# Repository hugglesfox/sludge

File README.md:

# Sludge

Sludge is a hardware platform which is compatible with
[SlimeVR](https://slimevr.dev) firmware. Sludge is designed to be as
featureless and cost down as reasonable to provide a cheaper and updated
alternative to the official SlimeVR hardware.

## Features

- ESP32-C3 + Bosch BMI160
- Powered by a swappable AA battery
- Firmware flashing and hardware debugging over USB

## Does not feature

- Battery charging
- Expansion modules (e.g. for easier foot rotation tracking)

## TODO

- [X] General electrical design
- [ ] Clean up silk screen
- [ ] Switch to USB-C
- [ ] Physical design (straps, casing, etc.)
- [ ] Real world testing

## Licensing

Sludge (c) by Hayley Hughes and Contributors

Sludge is licensed under a
Creative Commons Attribution-ShareAlike 4.0 International License.

You should have received a copy of the license along with this
work. If not, see <http://creativecommons.org/licenses/by-sa/4.0/>.

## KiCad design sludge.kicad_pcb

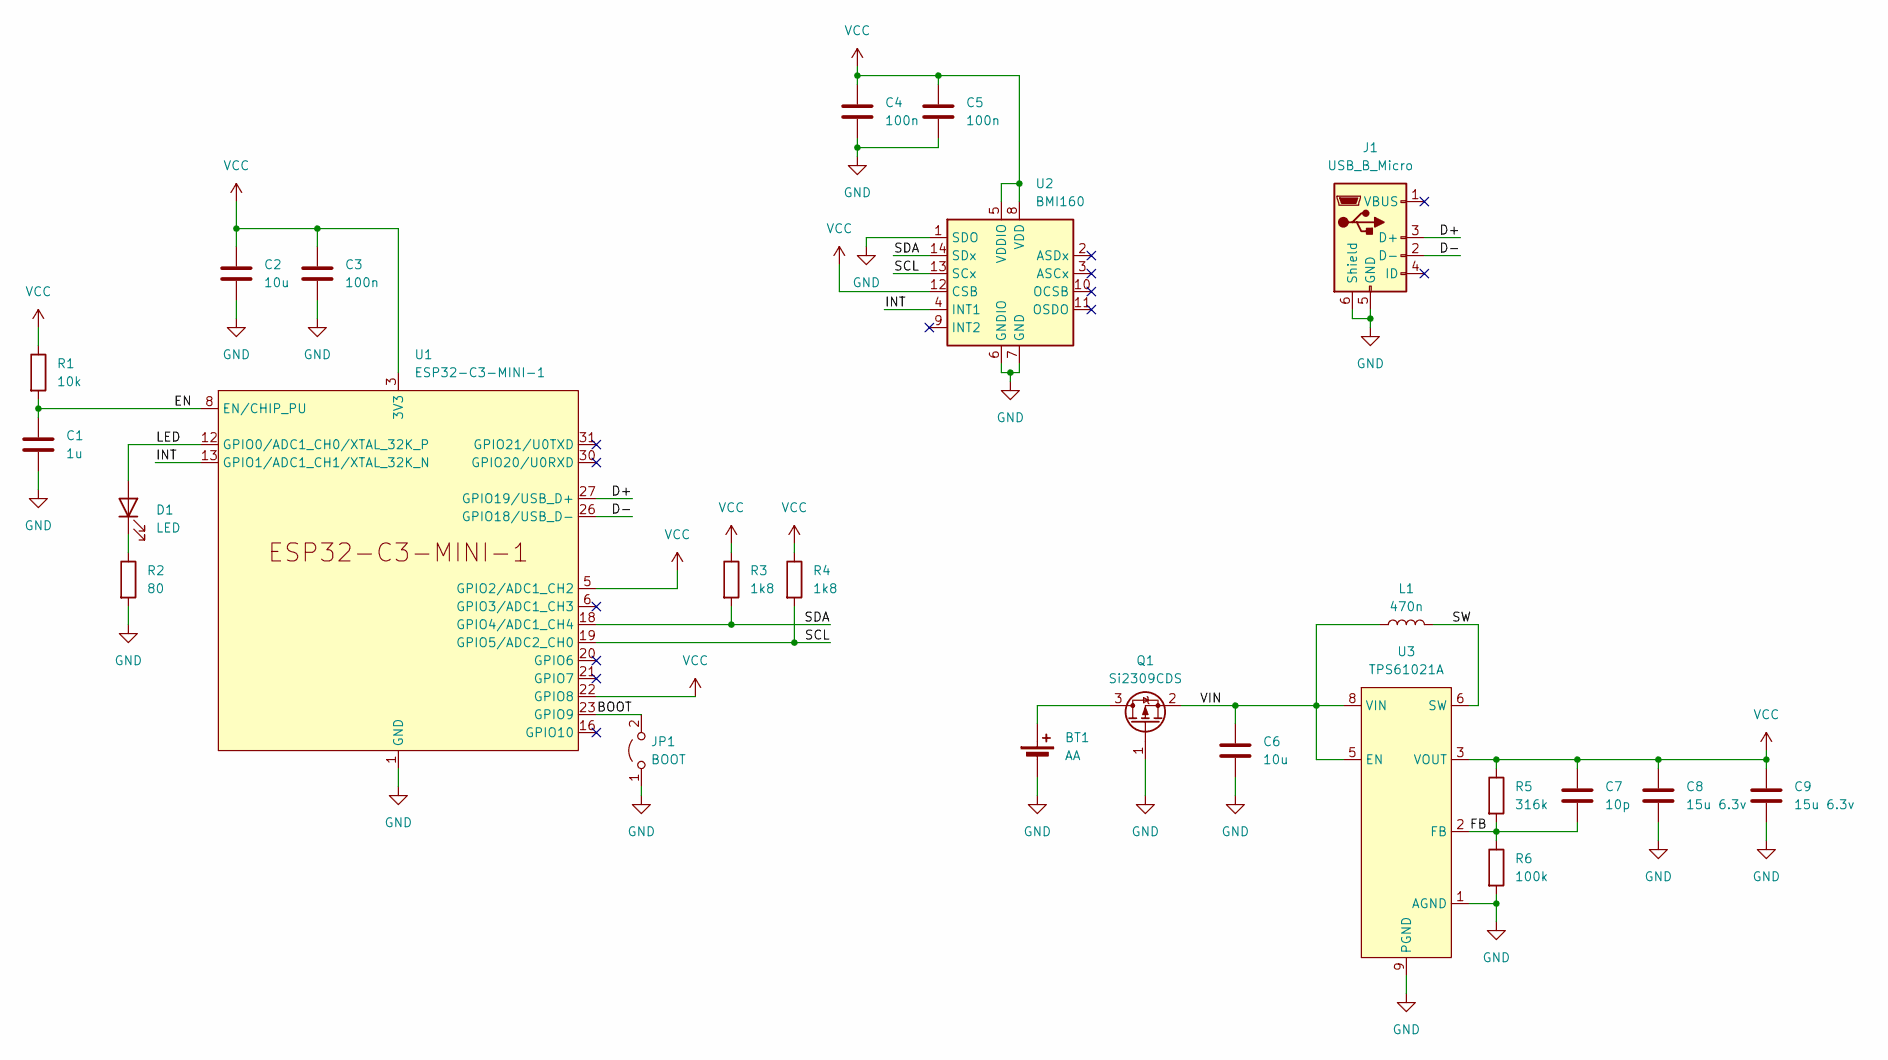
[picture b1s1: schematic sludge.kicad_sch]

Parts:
BT1: AA; BatteryHolder_Keystone_2460_1xAA
C1: 1u; C_0402_1005Metric
C2, C6: 10u; C_0402_1005Metric
C3, C4, C5: 100n; C_0402_1005Metric
C7: 10p; C_0402_1005Metric
C8, C9: 15u 6.3v; C_0603_1608Metric; JLCPCB Part # C445715
D1: LED; LED_1206_3216Metric; JLCPCB Part # C2764893
J1: USB_B_Micro; USB_Micro-B_Amphenol_10104110_Horizontal; JLCPCB Part # C2931352
JP1: BOOT; SolderJumper-2_P1.3mm_Open_TrianglePad1.0x1.5mm
L1: 470n; L_1008_2520Metric; JLCPCB Part # C237552
Q1: Si2309CDS; SOT-23; JLCPCB Part # C10493
R1: 10k; R_0402_1005Metric
R2: 80; R_0402_1005Metric
R3, R4: 1k8; R_0402_1005Metric
R5: 316k; R_0402_1005Metric
R6: 100k; R_0402_1005Metric
U1: ESP32-C3-MINI-1; JLCPCB Part # C5290152
U2: BMI160; Bosch_LGA-14_3x2.5mm_P0.5mm; JLCPCB Part # C94021
U3: TPS61021A; WSON-8-1EP_2x2mm_P0.5mm_EP0.9x1.6mm_ThermalVias; JLCPCB Part # C193037

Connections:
/BOOT: JP1.2 (B), U1.23 (GPIO9)
/D+: J1.3 (D+), U1.27 (GPIO19/USB_D+)
/D-: J1.2 (D-), U1.26 (GPIO18/USB_D-)
/EN: C1.1, R1.2, U1.8 (EN/CHIP_PU)
/FB: C7.2, R5.2, R6.1, U3.2 (FB)
/INT: U1.13 (GPIO1/ADC1_CH1/XTAL_32K_N), U2.4 (INT1)
/LED: D1.2 (A), U1.12 (GPIO0/ADC1_CH0/XTAL_32K_P)
/SCL: R4.2, U1.19 (GPIO5/ADC2_CH0), U2.13 (SCx)
/SDA: R3.2, U1.18 (GPIO4/ADC1_CH4), U2.14 (SDx)
/SW: L1.2, U3.6 (SW), U3.7 (SW)
/VIN: C6.1, L1.1, Q1.2 (S), U3.5 (EN), U3.8 (VIN)
GND: BT1.2 (-), C1.2, C2.2, C3.2, C4.2, C5.2, C6.2, C8.2, C9.2, J1.5 (GND), J1.6 (Shield), JP1.1 (A), Q1.1 (G), R2.2, R6.2, U1.1 (GND), U1.2 (GND), U1.11 (GND), U1.14 (GND), U1.36 (GND), U1.37 (GND), U1.38 (GND), U1.39 (GND), U1.40 (GND), U1.41 (GND), U1.42 (GND), U1.43 (GND), U1.44 (GND), U1.45 (GND), U1.46 (GND), U1.47 (GND), U1.48 (GND), U1.49 (GND), U1.50 (GND), U1.51 (GND), U1.52 (GND), U1.53 (GND), U2.1 (SDO), U2.6 (GNDIO), U2.7 (GND), U3.1 (AGND), U3.9 (PGND)
unnamed: BT1.1 (+), Q1.3 (D)
unnamed: D1.1 (K), R2.1
VCC: C2.1, C3.1, C4.1, C5.1, C7.1, C8.1, C9.1, R1.1, R3.1, R4.1, R5.1, U1.3 (3V3), U1.5 (GPIO2/ADC1_CH2), U1.22 (GPIO8), U2.5 (VDDIO), U2.8 (VDD), U2.12 (CSB), U3.3 (VOUT), U3.4 (VOUT)

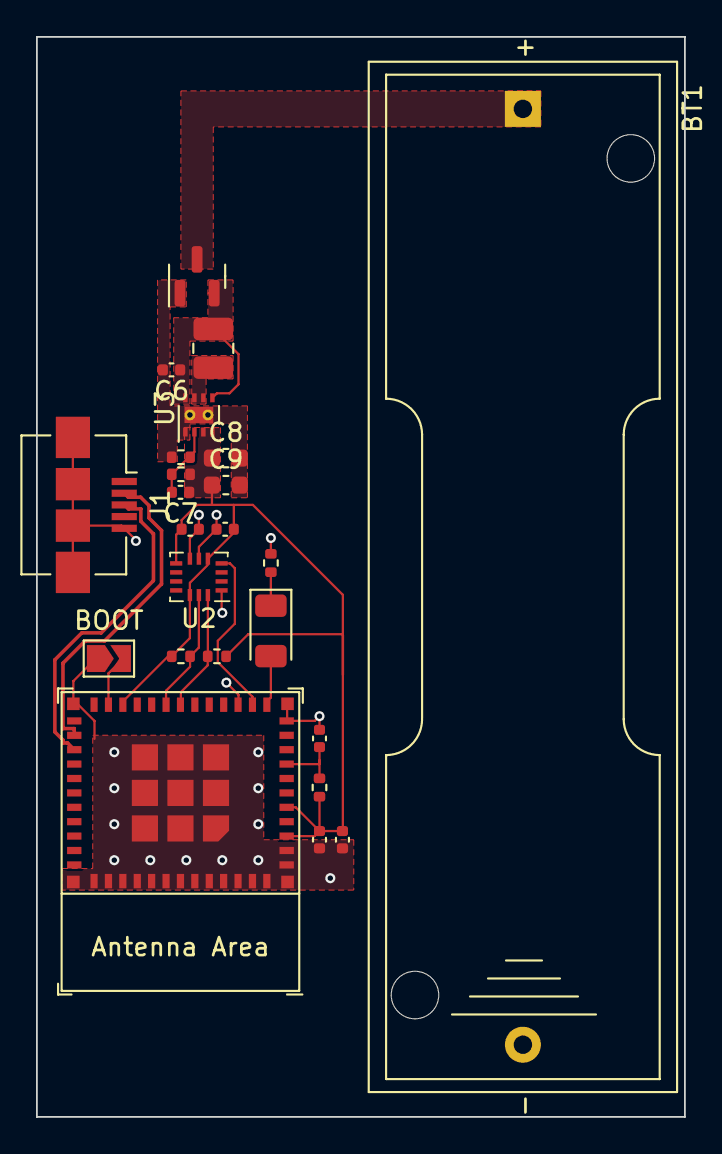
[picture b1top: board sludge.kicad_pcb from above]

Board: 2 copper layers, 36.0 x 60.0 mm, 24 parts (0 on the bottom side), 15 nets.
